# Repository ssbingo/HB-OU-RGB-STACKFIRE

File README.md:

# HB-OU-RGB-STACKFIRE - Kaminfeuer Leuchte

Viele Projekte haben sich mit der Steuerung von WS2812B-LED's befasst. 
Eigentlich wollte ich aus dem Tee-Licht-Projekt vom [pafra-123](https://github.com/pafra-123/HB_LED_Teelicht) einen kleinen Kamin für die Weihnachtskrippe machen.
Daraus enstand der Gedanke an eine etwas größere Kamin-/Lagerfeuer-Simulation. 
Irgendwo fand ich dann das Projekt einer Nachttischlampe.
Im Großen und Ganzen ganz hübsch, mir jedoch zu klein. Ich wollte es als Raumdeko, als Hingucker bei der Gartenparty und als gemütliches Highlight abends vor dem Wohnwagen. Und ich wollte es Homematic-gebunden haben. Da fand ich den [RGB-Controler](https://github.com/jp112sdl/HB-UNI-RGB-LED-CTRL) von Jérôme(jp112sdl).<br>
So verschmolzen Teile diverser Projekte zu einem Neuen.

## Bilder

## Konfiguration
### auf der Platine
Die aktuelle Version der PCB verfügt über einen 2-fach Jumper J4 (VCC). Dieser ermöglicht es, die Leuchte ohne das [AZDelivery 5 x 220V zu 5V Mini-Netzteil](https://www.amazon.de/gp/product/B07V7GHK51/ref=ppx_yo_dt_b_asin_title_o06_s00?ie=UTF8&psc=1) zu betreiben. Die Schaltung wird dann über das erste Netzteil der Stripes mit versorgt.<br>
:exclamation:Die Jumper dürfen auf keinen Fall gesteckt werden, wenn das Mini-Netzteil auf der Platine verbaut ist.
Mit dem Einsatz des Mini-Netzteiles habe ich die Möglichkeit, über den im Boden eingauten Schalter, die Netzteile der LED's abzuschalten, ohne dabei den Mega2560 vom Netz zu nehmen. Es kommen somit keine Servicemeldungen über ein "nicht erreichbares Gerät"

### im SourceCode
Die Leuchte ist so geplant, dass sie entwerder mit 10 Stripes á 30LED's oder mit 20 Stripes á 30LED's bestückt werden kann.
Die beiden Netzteile im Grundgehäuse versorgen jeweils immer jeden 2. Ausgang.<br>
Das Grundgehäuse hat für die Befestigung der Netzteile entsprechende Bohrungen(Abstandshalter).<br><br>

In Zeile 20 muss bei voller Bestückung der Paramter<br> #define doubleLED<br> gesetzt werden.<br> Bei halber Bestückung entsprechend auskommentieren.<br><br>

Die Zeilen 30-75 definieren die Anzahl der LED's je Stripe sowie die entsprechenden Ports der Arduino Mega 2560 Core.<br><br>

In den Zeilen 88-117 kann das Verhalten des FireProgramm's in Intensität (Sparking) und Flammenhöhe (Cooling) nach Bedarf angepasst werden.
Derzeit sind nur die letzten 3 Programme (Lagerfeuer, Wasserfall, TV-Simulation) als Feuer verknüpft.<br>
siehe: RGBCtrl.h Zeile 748-772 RGBProgramFire1(brightness,"1-6");<br><br>

In den Zeilen 123-144: FastLED liefert von Haus aus diverse Farbpaletten mit. Für ein Lagerfeuer haben sich bisher Nr.10 (HeatColors_p) oder Nr.11 (LavaColors_p) bewährt.<br><br>

## Schaltplan

[:arrow_right: Schaltplan](Images/PCB_HB-OU-RGB-STACKFIRE/Schaltplan_HB-OU-RGB-STACKFIRE-V2.pdf)

## Platine

[:arrow_right: PCB Gerber](Platine/HB-OU-RGB-STACKFIRE(Mega2560)-V2/HB-OU-RGB-STACKFIRE-V2.zip)

## Gehäuse

Das Gehaäuse ist ein 3D-Druck. Auf Grund der Größe ist hier mindestens ein Druckbereich von 220x220x200 erforderlich.
(ANET A8/A6/A10 o.ä).
Der Sockel besteht auf dem [Grundgehäuse](Gehäuse/Stack-Fire-Leuchte_Sockel_V1.stl) und der [Auflageplatte](Gehäuse/Stack-Fire-Leuchte_Sockel_Platine_V1.stl) für de Platine.
Desweiteren werden noch 2 Abschlussdeckel [oben](Gehäuse/Stack-Fire-Leuchte_Deckel_ALU_oben_V1.stl) und [unten](Gehäuse/Stack-Fire-Leuchte_Deckel_ALU_unten_V1.stl) für das AluRohr benötigt. 
Ich nutze zum drucken PETG. 

## Aufbau / Stückliste

### Der Aufbau

Grundgehäuse mit Netzteilen<br>

Auflage für die Platine<br>

Einbau der Auflage mit Verschraubung des Rohrhalters<br>

Rohrdeckel mit Verschraubung<br>

Montage des Alurohrs (dieses wird vor Anbringen der LED-Stripes komplett mit dem Wärmeleitklebeband beklebt<br>

Rohr mit voller Bestückung 20x30LED<br>

Testaufbau Teil 1<br>

Testbaubau Teil 2<br>

Testaufbau Teil 3<br>

Das Plexiglasrohr. Dieses wird am Ende einfach auf das Grundgehäuse gesteckt und kann bei Bedarf mit 4 Schrauben fixiert werden.<br>

Der passende Deckel kann direkt mit bestellt werden. Er ist so gefrässt, dass er passgenau auf das Rohr geklebt werden kann<br>

Prototype der WS2812B-Protect Platine. Diese wird nach der Bestückung direkt an den Stripe gelötet. Als Steckverbinder habe ich von gewinkelten Pinleisten (Raster 2.54) einfach die Stifte einzeln genommen. Ist viel Fummelei... <br>

### Die benötigten Bauteile
| Bauteil | Link |
| --------|------|
|50cm Alurohr Länge: 0,5-3 m Aluminium Rohr Alu Profil Rundrohr AlMgSi0,5 Modellbau | [:arrow_right: Ebay](https://www.ebay.de/itm/Alurohr-L%C3%A4nge-0-5-3-m-Aluminium-Rohr-Alu-Profil-Rundrohr-AlMgSi0-5-Modellbau/222169076786?ssPageName=STRK%3AMEBIDX%3AIT&var=521010583605&_trksid=p2057872.m2749.l2649) |
|55cm  PLEXIGLAS® XT Rohr 3mm weiß 200/194mm Durchmesser | [:arrow_right: Ebay](https://www.ebay.de/itm/PLEXIGLAS-XT-Rohr-3mm-wei%C3%9F-200-194mm-Durchmesser-74-00-lfdm/112415674967?ssPageName=STRK%3AMEBIDX%3AIT&var=412812679722&_trksid=p2057872.m2749.l2649) |
|PLEXIGLAS® Deckel 4 mm weiß Ø freiwählbar passend für unsere PLEXIGLAS® XT Rohr | [:arrow_right: Ebay](https://www.ebay.de/itm/PLEXIGLAS-Deckel-4-mm-wei%C3%9F-%C3%98-freiw%C3%A4hlbar-passend-f%C3%BCr-unsere-PLEXIGLAS-XT-Rohre/122355660437?ssPageName=STRK%3AMEBIDX%3AIT&var=422838977364&_trksid=p2057872.m2749.l2649)|
|WS2812B-Protect | [:arrow_right: Reichelt Bestell-Liste](https://www.reichelt.de/my/1667564) |
|Limeow Thermisch Klebeband Wärmeleitendes Doppelseitiges Klebeband Selbstklebend Tape Wärmeleitpaste Thermal Compound Thermische Verbindung Paste Kühlkörper Leitfähiges Kühlband Doppelseitig Klebend | [:arrow_right: Amazon](https://www.amazon.de/gp/product/B07FPKVML7/ref=ppx_yo_dt_b_asin_title_o05_s00?ie=UTF8&psc=1) |
|AZDelivery 5 x 220V zu 5V Mini-Netzteil für Arduino und Raspberry Pi | [:arrow_right: Amazon](https://www.amazon.de/gp/product/B07V7GHK51/ref=ppx_yo_dt_b_asin_title_o06_s00?ie=UTF8&psc=1) |
|MW LRS-150F-5 Schaltnetzteil, geschlossen, 110 W, 5 V, 22 A | [:arrow_right: Reichelt](https://www.reichelt.de/schaltnetzteil-geschlossen-110-w-5-v-22-a-mw-lrs-150f-5-p202979.html?&nbc=1)|
| | |
|Bauteileliste Reichelt (incl. der benötigten Netzteile)| [:arrow_right: Reichelt](https://www.reichelt.de/my/1677743)|

## Hinweise

- :exclamation: Viele Projekte verweisen auf Probleme mit dem WS2812B. Die Schutzschaltung WS2812B-Protect ist eine kleine 17x10mm Platine, welche die Stripes schützen soll. Sie ist je nach eigenem Ermessen einbaubar. 

## CCU2/CCU3/RaspberryMatic Installation

Einstellungen/Systemsteuerung/Zusatzsoftware -> Datei 

Ich nutze das AddOn von Jérôme (jp112sdl) [JP-HB-Devices-addon](https://github.com/jp112sdl/JP-HB-Devices-addon).
In dieses bzw. dessen Struckture müssen die Dateien aus dem Verzeichniss [AddOn](AddOn) entsprechend selbst eingebunden werden und das AddOn dann installiert werden.

## Benötige Libraries

 - [FastLED](https://github.com/FastLED/FastLED)
 - [AskSinPP](https://github.com/pa-pa/AskSinPP)
   - sowie die dort aufgeführten [zusätzlichen Bibliotheken](https://github.com/pa-pa/AskSinPP#required-additional-arduino-libraries)

## Lizenz

**Creative Commons BY-NC-SA**<br>
Give Credit, NonCommercial, ShareAlike

<br />This work is licensed under a <a rel="license" href="http://creativecommons.org/licenses/by-nc-sa/4.0/">Creative Commons Attribution-NonCommercial-ShareAlike 4.0 International License</a>.

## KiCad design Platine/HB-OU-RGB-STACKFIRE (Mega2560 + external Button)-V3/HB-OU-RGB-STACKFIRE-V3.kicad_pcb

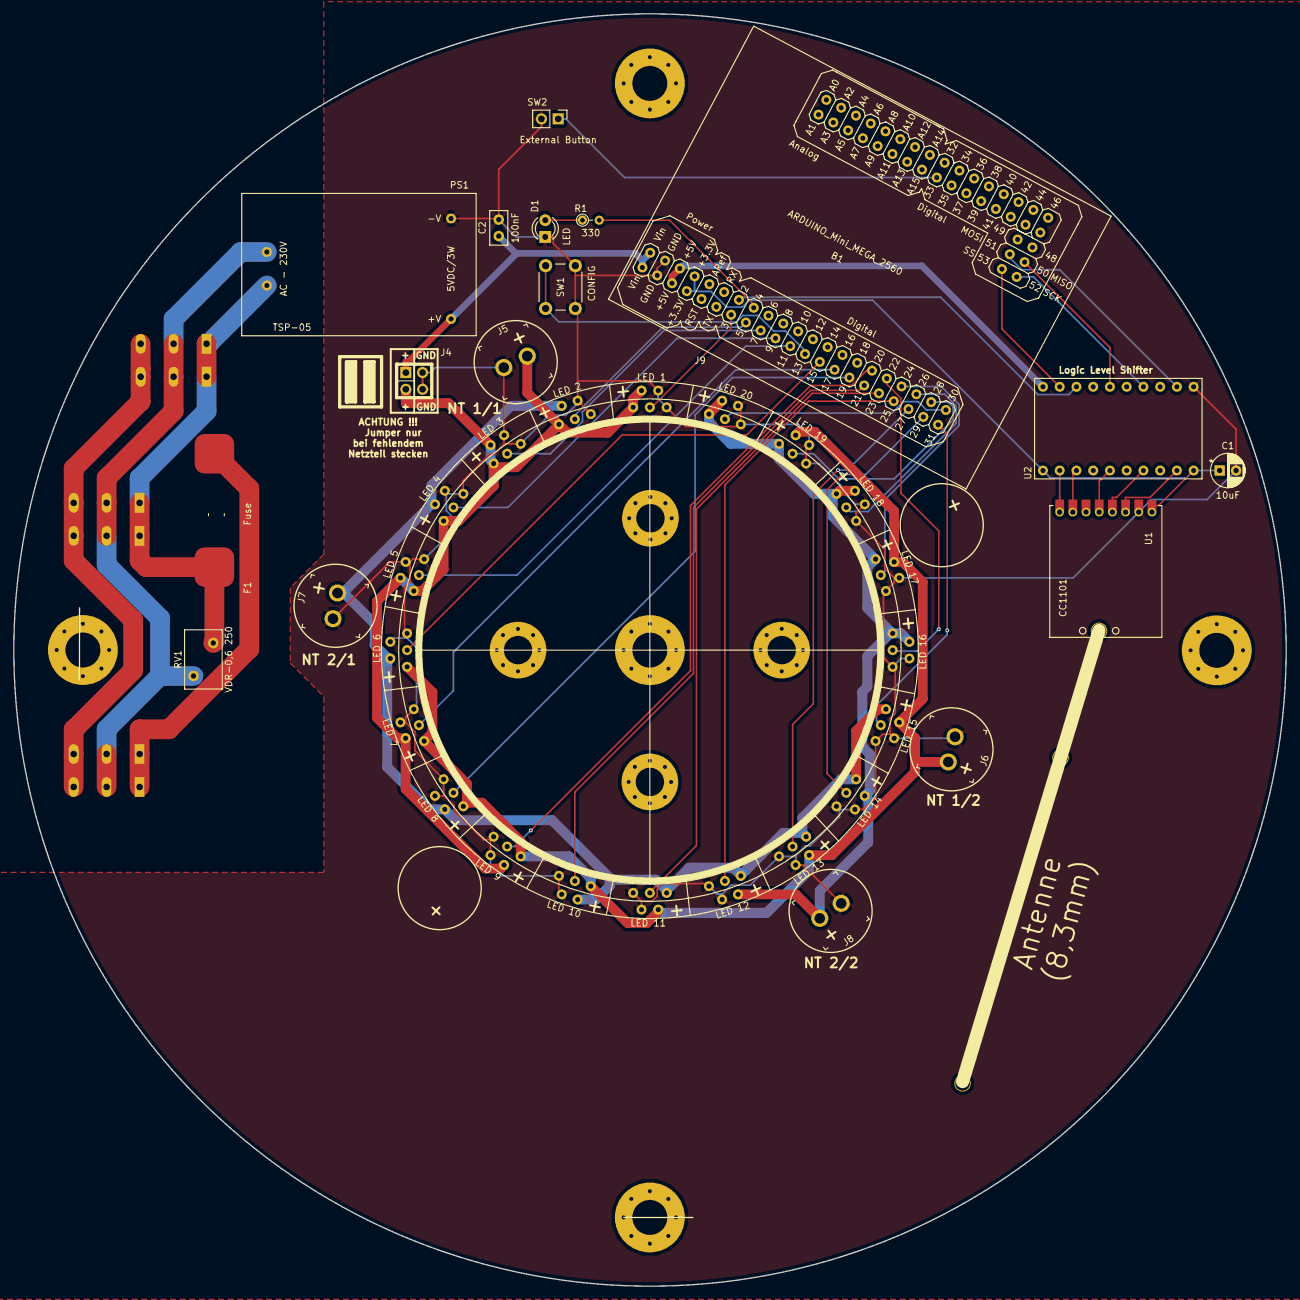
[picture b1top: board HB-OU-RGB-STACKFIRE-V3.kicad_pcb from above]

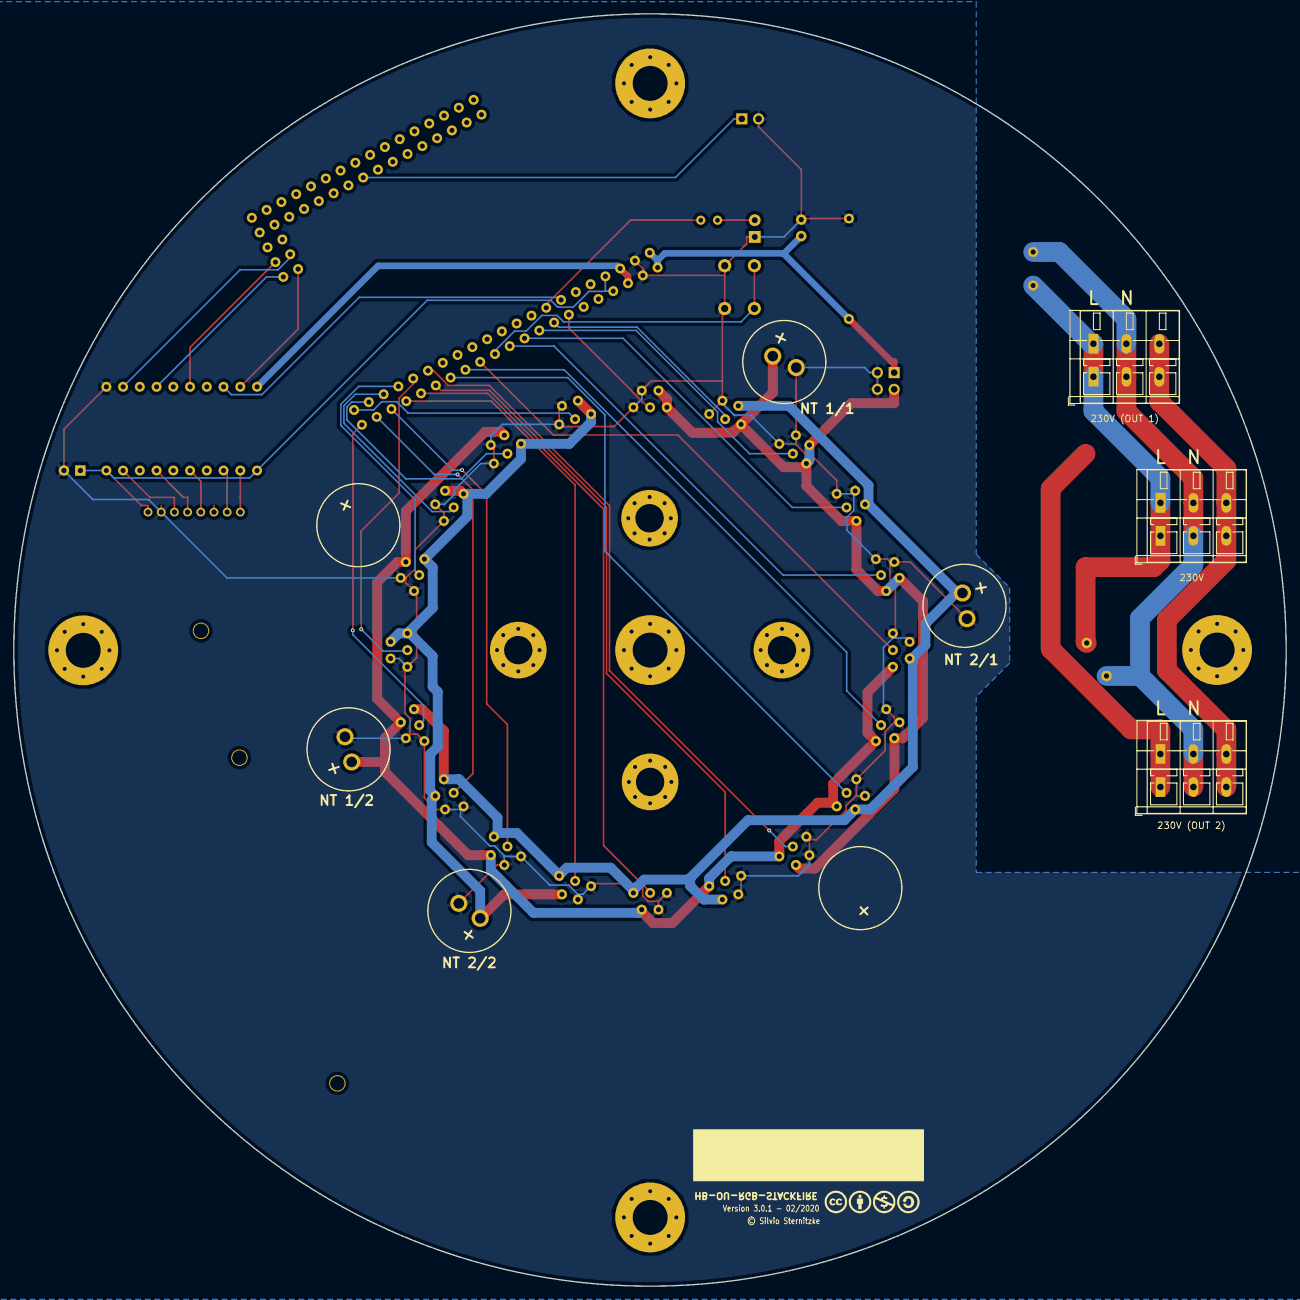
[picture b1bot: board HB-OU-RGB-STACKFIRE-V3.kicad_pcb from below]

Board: 2 copper layers, 193.0 x 193.0 mm, 34 parts (3 on the bottom side), 46 nets.

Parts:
B1: ARDUINO_Mini_MEGA_2560; Mini Mega 2560
C1: 10uF; CP_Radial_D5.0mm_P2.50mm
C2: 100nF; C_Disc_D5.0mm_W2.5mm_P2.50mm
Cp1: Version 3.0.1 - 02/2020; Copyrigth
D1: LED; LED_D3.0mm
F1: Fuse; Fuse_Schurter_318265
J1: 230V (OUT 1); TerminalBlock_WAGO_236-103_1x03_P5.00mm_45Degree
J2: 230V; TerminalBlock_WAGO_236-103_1x03_P5.00mm_45Degree
J3: 230V (OUT 2); TerminalBlock_WAGO_236-103_1x03_P5.00mm_45Degree
J4: VCC; PinHeader_2x02_P2.54mm_Vertical
J5, J6, J7, J8: 5V - WS28XX; PinHeader_1x2_P3.96mm_Drill1.6mm
J9: Stackfire-Ring
MH1, MH2, MH3: MountingHole_2.2mm_M2_Pad
P1, P2, P3, P4, P5: MountingHole_5.3mm_M5_Pad_Via
P11, P12, P13, P14: MountingHole_4.3mm_M4_Pad_Via
PS1: TSP-05
R1: 330; R_Axial_DIN0204_L3.6mm_D1.6mm_P2.54mm_Vertical
RV1: VDR-0,6 250; RV_Disc_D9mm_W5.7mm_P5mm
SW1: CONFIG; SW_PUSH_6mm_H5mm
SW2: External Button; PinHeader_1x02_P2.54mm_Vertical
U1: CC1101
U2: 8-Kanal_LevelShifter; Adafruit 8-Kanal Level Shifter

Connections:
+3V3: B1.3.3V, C1.1, U1.1, U2.1, U2.10
+5V: B1.5V@0, B1.5V@1, U2.11
+VDC: B1.VIN, C2.1, J4.1, PS1.4
/HV1(MISO): B1.50, U2.15
/HV2(MOSI): B1.51, U2.19
/HV3(SCK): B1.52, U2.17
/HV4(SS): B1.53, U2.12
/HV5(D2): B1.2, U2.13
/LV1(MISO): U1.5, U2.5
/LV2(MOSI): U1.3, U2.9
/LV3(SCK): U1.4, U2.7
/LV4(SS): U1.8, U2.2
/LV5(D2): U1.7, U2.3
/VCC_WS28XX_1_1: J4.3, J5.2, J9.3, J9.6, J9.9, J9.12, J9.15, J9.62, J9.66, J9.70, J9.74, J9.78
/VCC_WS28XX_1_2: J6.2, J9.18, J9.21, J9.24, J9.27, J9.30, J9.82, J9.86, J9.90, J9.94, J9.98
/VCC_WS28XX_2_1: J7.2, J9.33, J9.36, J9.39, J9.42, J9.45, J9.64, J9.68, J9.72, J9.76, J9.80
/VCC_WS28XX_2_2: J8.2, J9.48, J9.51, J9.54, J9.57, J9.60, J9.84, J9.88, J9.92, J9.96, J9.100
/WS28XX_1: B1.3, J9.2
/WS28XX_2: B1.5, J9.5
/WS28XX_3: B1.7, J9.8
/WS28XX_4: B1.9, J9.11
/WS28XX_5: B1.11, J9.14
/WS28XX_6: B1.15, J9.17
/WS28XX_7: B1.17, J9.20
/WS28XX_8: B1.19, J9.23
/WS28XX_9: B1.20, J9.26
/WS28XX_10: B1.21, J9.29
/WS28XX_11: B1.23, J9.32
/WS28XX_12: B1.25, J9.35
/WS28XX_13: B1.27, J9.38
/WS28XX_14: B1.29, J9.41
/WS28XX_15: B1.31, J9.44
/WS28XX_16: B1.22, J9.47
/WS28XX_17: B1.24, J9.50
/WS28XX_18: B1.26, J9.53
/WS28XX_19: B1.28, J9.56
/WS28XX_20: B1.30, J9.59
GND: B1.GND@, C1.2, C2.2, D1.1, J4.2, J4.4, J5.1, J6.1, J7.1, J8.1, J9.1, J9.4, J9.7, J9.10, J9.13, J9.16, J9.19, J9.22, J9.25, J9.28, J9.31, J9.34, J9.37, J9.40, J9.43, J9.46, J9.49, J9.52, J9.55, J9.58, J9.61, J9.63, J9.65, J9.67, J9.69, J9.71, J9.73, J9.75, J9.77, J9.79, J9.81, J9.83, J9.85, J9.87, J9.89, J9.91, J9.93, J9.95, J9.97, J9.99, PS1.3, SW1.2, SW2.2, U1.2, U2.20
unnamed: B1.4, R1.2
unnamed: B1.13, SW1.1
unnamed: B1.33, SW2.1
unnamed: D1.2, R1.1
unnamed: F1.1, J3.1
unnamed: F1.2, J1.1, J2.1, PS1.2, RV1.1
unnamed: J1.2, J2.2, J3.2, PS1.1, RV1.2
unnamed: J1.3, J2.3, J3.3

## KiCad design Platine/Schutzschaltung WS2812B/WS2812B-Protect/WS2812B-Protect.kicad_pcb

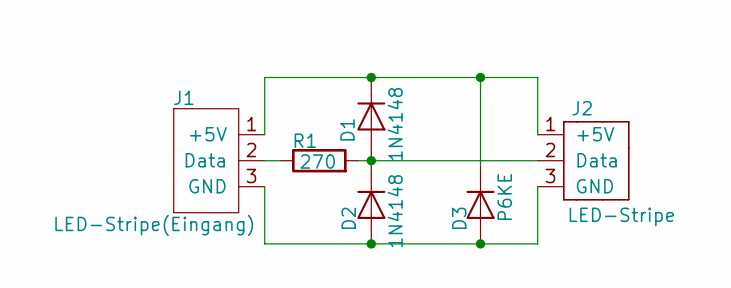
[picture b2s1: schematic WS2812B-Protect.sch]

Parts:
D1, D2: 1N4148; D_SOD-323F
D3: P6KE; D_2114_3652Metric_Castellated
J1: LED-Stripe(Eingang); PinHeader_1x03_P2.54mm_Horizontal
J2: LED-Stripe
R1: 270; R_0805_2012Metric

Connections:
unnamed: D1.1 (K), D3.1 (K), J1.1 (+5V), J2.1 (+5V)
unnamed: D1.2 (A), D2.1 (K), J2.2 (Data), R1.2
unnamed: D2.2 (A), D3.2 (A), J1.3 (GND), J2.3 (GND)
unnamed: J1.2 (Data), R1.1

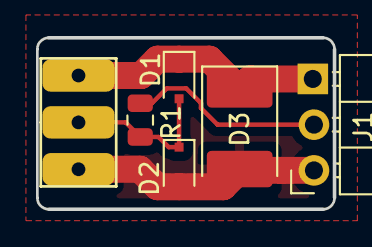
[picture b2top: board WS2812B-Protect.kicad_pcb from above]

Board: 2 copper layers, 16.5 x 9.5 mm, 7 parts (0 on the bottom side), 4 nets.

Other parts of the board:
V1: Version 1.0.2; Copyrigth

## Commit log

2020-02-01 AddOn
    AddOn
2020-02-01 Image PCB
2020-02-02 Images Aufbau
2020-02-16 Images Testaufbau
2020-02-18 Testaufbau
2020-02-18 Images
2020-02-18 del ws2812B
2020-02-24 Rev 3.0.1 wit external Button (Test)
2020-02-24 xml with internal Key
2020-02-24 cosmetic
2020-02-24 readme.md
2020-02-24 pic klein
2020-02-25 Plexi
2020-02-25 Image

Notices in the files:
Platine/HB-OU-RGB-STACKFIRE (Mega2560 + external Button)-V3/HB-OU-RGB-STACKFIRE-V3.kicad_pcb:
©S. Sternitzke
parts and their libraries:
© Silvio Sternitzke
